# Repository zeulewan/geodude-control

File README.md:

# GEO-DUDe Control

Hardware photo:

GUI demo:

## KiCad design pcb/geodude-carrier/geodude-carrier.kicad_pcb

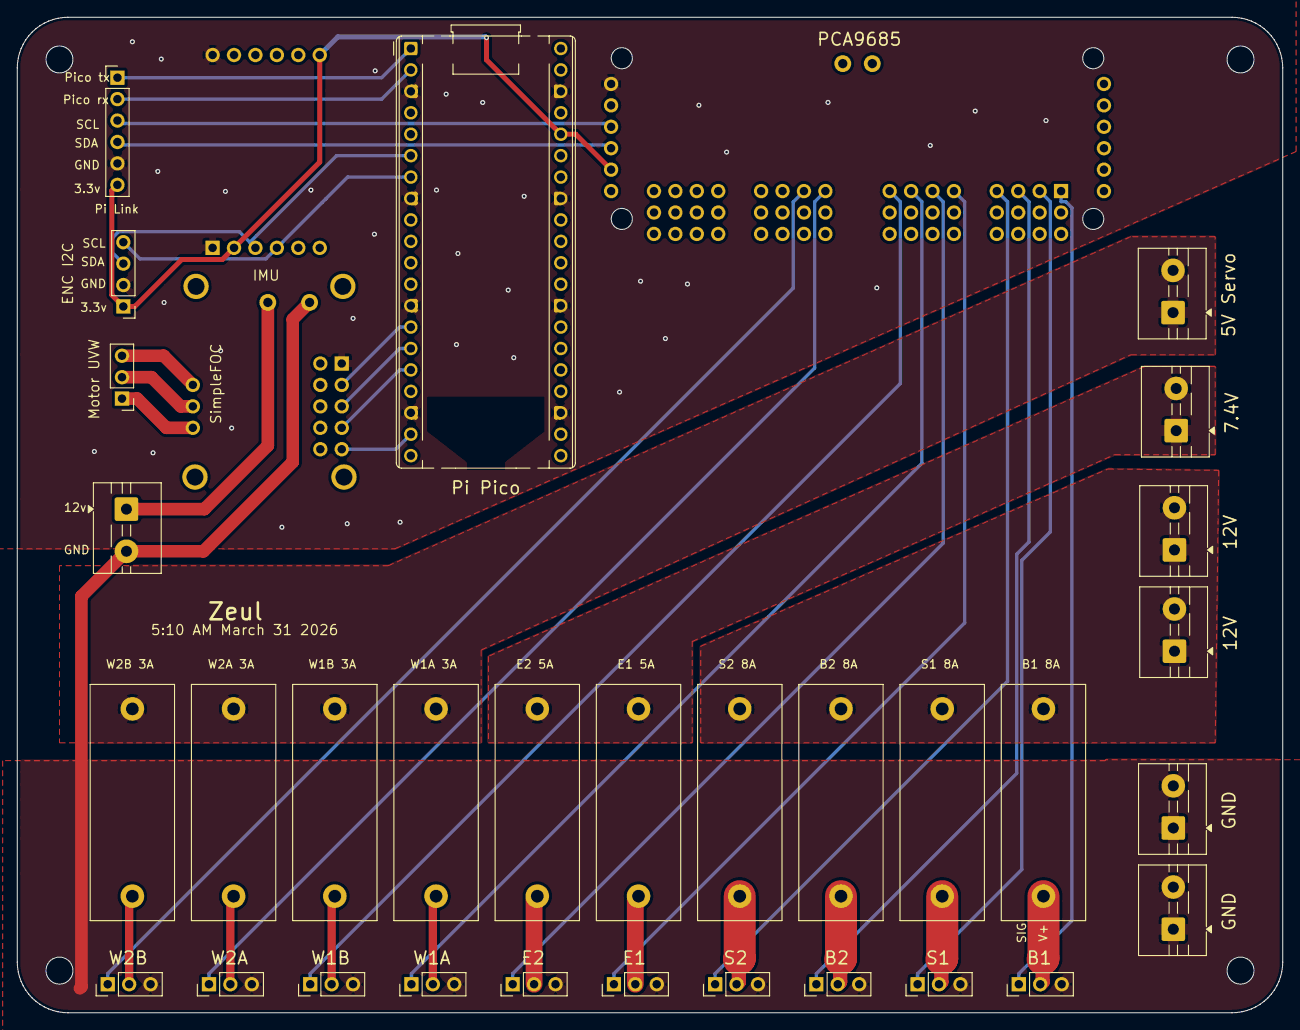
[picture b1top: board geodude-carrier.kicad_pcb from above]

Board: 2 copper layers, 150.0 x 118.0 mm, 38 parts (1 on the bottom side), 40 nets.

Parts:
F1: B1 8A; BLX-A_5x20mm
F2: S1 8A; BLX-A_5x20mm
F3: E1 5A; BLX-A_5x20mm
F4: W1A 3A; BLX-A_5x20mm
F5: W1B 3A; BLX-A_5x20mm
F6: B2 8A; BLX-A_5x20mm
F7: S2 8A; BLX-A_5x20mm
F8: E2 5A; BLX-A_5x20mm
F9: W2A 3A; BLX-A_5x20mm
F10: W2B 3A; BLX-A_5x20mm
J1, J2: 12V; TerminalBlock_MaiXu_MX126-5.0-02P_1x02_P5.00mm
J3, J4: GND; TerminalBlock_MaiXu_MX126-5.0-02P_1x02_P5.00mm
J5: 7.4V; TerminalBlock_MaiXu_MX126-5.0-02P_1x02_P5.00mm
J6: 5V Servo; TerminalBlock_MaiXu_MX126-5.0-02P_1x02_P5.00mm
J_ENC: ENC I2C; PinHeader_1x04_P2.54mm_Vertical
J_FOC: SimpleFOC; SimpleFOC_Mini
J_FOC_12V: 12V FOC; TerminalBlock_MaiXu_MX126-5.0-02P_1x02_P5.00mm
J_IMU: IMU; SparkFun_ICM20948
J_MOTOR: Motor UVW; PinHeader_1x03_P2.54mm_Vertical
J_PCA: PCA9685; PCA9685_Breakout
J_PICO: Pi Pico; RaspberryPi_Pico_Common_THT
J_SERIAL: Pi Link; PinHeader_1x06_P2.54mm_Vertical
MH1, MH2, MH3, MH4: M3; MountingHole_3.2mm_M3
SV1: B1; PinHeader_1x03_P2.54mm_Vertical
SV2: S1; PinHeader_1x03_P2.54mm_Vertical
SV3: E1; PinHeader_1x03_P2.54mm_Vertical
SV4: W1A; PinHeader_1x03_P2.54mm_Vertical
SV5: W1B; PinHeader_1x03_P2.54mm_Vertical
SV6: B2; PinHeader_1x03_P2.54mm_Vertical
SV7: S2; PinHeader_1x03_P2.54mm_Vertical
SV8: E2; PinHeader_1x03_P2.54mm_Vertical
SV9: W2A; PinHeader_1x03_P2.54mm_Vertical
SV10: W2B; PinHeader_1x03_P2.54mm_Vertical

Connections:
+3V3: J_ENC.1, J_IMU.2, J_IMU.12, J_PCA.56, J_PICO.36, J_SERIAL.6
+5V_SERVO: F4.1, F5.1, F9.1, F10.1, J6.1, J6.2
+7V4: F3.1, F8.1, J5.1, J5.2
+12V: F1.1, F2.1, F6.1, F7.1, J1.1, J1.2, J2.1, J2.2
+12V_FOC: J_FOC.15, J_FOC_12V.1
FOC_EN: J_FOC.3, J_PICO.14
FOC_IN1: J_FOC.9, J_PICO.19
FOC_IN2: J_FOC.7, J_PICO.16
FOC_IN3: J_FOC.5, J_PICO.15
GND: J3.1, J3.2, J4.1, J4.2, J_FOC.14, J_FOC_12V.2, SV1.3, SV2.3, SV3.3, SV4.3, SV5.3, SV6.3, SV7.3, SV8.3, SV9.3, SV10.3
GND_LOGIC: J_ENC.2, J_FOC.1, J_IMU.1, J_IMU.7, J_PCA.60, J_PICO.3, J_PICO.8, J_PICO.13, J_PICO.18, J_PICO.23, J_PICO.28, J_PICO.33, J_PICO.38, J_SERIAL.5
MOTOR_U: J_FOC.11, J_MOTOR.3
MOTOR_V: J_FOC.12, J_MOTOR.2
MOTOR_W: J_FOC.13, J_MOTOR.1
PICO_RX: J_PICO.2, J_SERIAL.2
PICO_SCL: J_ENC.4, J_IMU.4, J_PICO.7
PICO_SDA: J_ENC.3, J_IMU.3, J_PICO.6
PICO_TX: J_PICO.1, J_SERIAL.1
PWM_CH0: J_PCA.1, SV1.1
PWM_CH1: J_PCA.4, SV2.1
PWM_CH2: J_PCA.7, SV6.1
PWM_CH3: J_PCA.10, SV7.1
PWM_CH4: J_PCA.13, SV3.1
PWM_CH5: J_PCA.16, SV8.1
PWM_CH6: J_PCA.19, SV4.1
PWM_CH7: J_PCA.22, SV5.1
PWM_CH8: J_PCA.25, SV9.1
PWM_CH9: J_PCA.28, SV10.1
SCL: J_PCA.58, J_SERIAL.3
SDA: J_PCA.57, J_SERIAL.4
SV1_PWR: F1.2, SV1.2
SV2_PWR: F2.2, SV2.2
SV3_PWR: F3.2, SV3.2
SV4_PWR: F4.2, SV4.2
SV5_PWR: F5.2, SV5.2
SV6_PWR: F6.2, SV6.2
SV7_PWR: F7.2, SV7.2
SV8_PWR: F8.2, SV8.2
SV9_PWR: F9.2, SV9.2
SV10_PWR: F10.2, SV10.2

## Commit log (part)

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2026-03-24 cd /home/mizi/geodude-dev/groundstationAdd camera stream toggle to dashboard fuser -k 8081/tcp || true (env WHEEL_CONTROL_PORT=8081 WHEEL_CONTROL_DRY_RUN=1 WHEEL_CONTROL_RESTORE_ON_START=0 nohup pyth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
2026-03-24 Bias dev IK toward stiffer wrist-assisted poses
2026-03-24 Update dev mission simulation flow
2026-03-24 Compact dev mission simulation layout
2026-03-24 Add EN active LOW and MS1/MS2 address table to TMC2209 driver label
2026-03-24 Fix screw terminal count: 2x 7.4V and 2x 5V inputs
2026-03-24 Add dev mission substep completion states
2026-03-25 Add dev approach arm positioning substeps
2026-03-25 Add dev AOCS attach mission substeps
2026-03-25 Enable mission arm view mouse controls
2026-03-25 Reorder dev identified-check substeps
2026-03-25 Checkpoint MACE control updates before branch merge
2026-03-25 MACE: RPM input, enable/disable/stop/calibrate buttons, voltage limit
2026-03-27 Fix All Neutral button: send PWM command to hardware
    chGoNeutral() was only updating the slider UI without calling
    chSendPwm(), so the button had no effect on actual servo positions.
2026-03-27 Gimbal firmware: OTA resilience, POST /reboot, driverFound cache, UART race guards
    Firmware (firmware/esp32/gimbal_controller.ino):
    - Cache per-driver found state (driverFound[4]); handleStatus returns the cached
    value during stepping so the dashboard stops flashing NOT FOUND while a motor
    is actually moving.
    - handleMotorIhold now applies the change to the driver immediately when the
    motor is idle-but-enabled. Previously the value was only stored in RAM and
2026-03-27 Servo safety v4: second audit findings (C-A, C-B, H-A..E, L-B, L-D, L-E, M-C..F)
    Second paranoid audit found that v3 still left a few holes. These fixes
    close them all.
    CRITICAL fixes:
    - C-A: Groundstation no longer blindly trusts accepted_pw returned from
    GEO-DUDe. Clamp to [0..2500] and to the per-channel envelope before
    assigning it to _servo_actual_pw. If the remote somehow returns a value
2026-03-27 Add pwm_seed to prevent 50us staircase on unpowered channels
    GEO-DUDe:
    - New POST /pwm_seed writes a requested pw directly to the PCA and sets
    _servo_last_pw in one step. Only accepted when the channel is currently
    unseeded (last_pw is None or 0); rejected with 409 if a live signal is
    present. Cannot be used to bypass the 50us delta clamp on a moving servo.
    Groundstation:
2026-03-30 Camera: 1280x960 4:3 uncropped
2026-03-30 Add brake button and RPM display
    Brake: sends 1000us (idle) but stays armed - ESC applies brake if enabled
    RPM: calculated from encoder angle deltas, 15-sample rolling average
2026-03-30 Fix arm button flicker: skip DOM updates when state unchanged
2026-03-30 Revert sensor loop to 30Hz — 100Hz caused I2C lock contention with motor writes
2026-03-30 Update gimbal ESP32 docs: pin assignments, UART wiring, network config
    - Corrected STEP/DIR pin assignments to match firmware (GPIO 32/33, 25/26, 23/22, 19/18)
    - Added UART pin assignment: GPIO 16 (RX) / GPIO 17 (TX) with 1K resistor
    - Documented BTT TMC2209 V1.3 single-wire UART wiring (factory default RX pin only)
    - Added ESP32 firmware details: web UI, OTA, WiFi, driver scanning, motor control
    - Added note that 24V on VM is required for UART communication
    - Updated base station with hostname, WiFi hotspot config, network architecture
2026-03-30 Fix carrier PCB schematic: 5 power rails, PCA9685 on 3.3V
    - +12V (servo power, ESC, fan)
    - +7V4 (elbow servo power)
    - +5V_SERVO (wrist servo power, from buck 3)
    - +5V_LOGIC (from Pi 5V, general purpose)
    - +3V3 (from Pi 3.3V, PCA9685 VCC, I2C bus)
2026-03-30 Generated netlist from SKiDL - all components and nets verified
2026-03-30 Custom BLX-A fuse footprint, updated PCB layout with paralleled 12V/GND
2026-03-30 Disable manual routing (traces cross), prepare for Freerouting
2026-03-30 Remove broken net class API call, widths via DSN patching only
2026-03-30 Replace single pin headers with 1x4 headers for bus section
2026-03-30 All power screw terminals in one line at top edge
2026-03-30 Layout: logic bus left edge, servo headers right edge, PCA top edge
2026-03-30 Logic bus: screw terminals in column left, headers column right
2026-03-30 Centre PCA socket properly (account for pin 1 origin offset)
2026-03-30 Centre servo row, centre ESC/Fan, bring fuses closer
2026-03-30 Sync generate_pcb.py: remove GND terminals
2026-03-30 Fix SV10 position, snap all components to grid
2026-03-30 Clean re-route: 254 tracks, no shorts, J1/J2 all +12V, silkscreen preserved
2026-03-30 Re-routed with default clearance, 2 unconnected remaining, via sizing needs work
2026-03-30 Add agent onboarding doc for new developers
2026-03-30 230 tracks, 1 unconnected (fan PWM - manual route needed), Gerbers updated
2026-03-30 Snap screw terminals in columns on each side
2026-03-30 Left bus: screw+header pairs aligned, 12mm spacing
2026-03-30 Routed, bigger silk, ESC/Fan fixed, Gerbers - 5 unconnected need manual route
2026-03-30 Wider board 128x149mm, 6mm rounded corners, fuses spread, 273 tracks, 0 unconnected
2026-03-30 Re-routed with adjusted edges, 253 tracks, 1 unconnected
2026-03-31 Board 140x134mm, fan +12V thin trace, render, 1 unconnected PWM, Gerbers ready
2026-03-31 Carrier PCB docs: SimpleFOC system, Pi Pico, IMU breakout, remove ESC
2026-03-31 Stripped for placement work
2026-03-31 Add deceleration ramp for smooth motor stopping
    Trapezoidal velocity profile: accelerate from 8000us to target
    step delay, cruise, then decelerate symmetrically. Prevents
    abrupt stops that caused motor oscillation on longer moves.
2026-03-31 Fix IHOLD=0: move begin() out of doScan() to prevent reset
    doScan() was calling begin() on all drivers, which reinitialized
    them and overwrote the IHOLD=0 register write. Split into
    initDrivers() (called once at boot) and doScan() (read-only).
2026-03-31 Revamp UI: tabbed layout, compact header, full gimbal parity
    - Tabbed navigation: GEO-DUDe / Gimbal / Servos
    - Always-visible header: camera (400px), system stats, sensor strip
    - Dual connection status dots (GEO-DUDe + Gimbal)
    - Wider layout (1200px max)
    - Gimbal tab: speed presets, current input, per-driver detail
    cards with OT/OTPW warnings, collapsible driver info,
2026-03-31 More compact: tighter padding, margins, gaps, font sizes
2026-03-31 Fix idle heating: force SpreadCycle + toff(0) at boot before any autoscale
2026-03-31 Smoother ramp: 4000us start (was 8000), 15% accel phase (was 25%)
2026-03-31 Add PCB agent onboarding docs (pcb/CLAUDE.md)
2026-04-01 Rate-limit servo slider movements with max velocity
    Slider drags no longer send PWM directly. A continuous ramp
    loop (30Hz) moves actual PWM toward the slider target at the
    configured max speed. Prevents jerky servo movements when
    dragging sliders quickly. Center and Neutral buttons also go
    through the same rate-limited path.
2026-04-01 Add ramp rate slider, persist speed settings, fix camera multi-client
    - Ramp rate slider back (controls center/neutral button speed)
    - Servo speed + ramp rate persist in localStorage across reloads
    - Camera: single reader thread fans out frames to all clients,
    fixes stream corruption when multiple browsers connect
2026-04-01 Store servo neutral positions server-side on disk
    Neutral positions saved to servo_neutral.json on the groundstation
    Pi. Survives page reloads, browser changes, and reboots.
2026-04-01 Order servos as Arm 1 (left) and Arm 2 (right) columns
2026-04-01 Safe servo startup: neutral on boot, remove dangerous center
    - sensor_server: remove pca_all_off() on boot, let groundstation
    send neutral positions instead of leaving servos limp
    - Restore loop sends neutral positions, not last-known
    - chActual defaults to neutral, not 1500
    - Remove ALL CENTER button and per-servo Center button (1500us
    fully extends arms, dangerous)
2026-04-01 Document network architecture, git workflow, multi-developer setup
2026-04-02 Refactor MACE reaction wheel control from ESC/PCA9685 to SimpleFOC/Pico USB serial
    - geodude/sensor_server.py: add /simplefoc endpoint that sends velocity commands
    to Pi Pico over USB serial (/dev/ttyACM0, 115200 baud) using SimpleFOC Commander
    protocol (T<value>\n). Legacy /motor endpoint kept, translates ESC PWM to velocity.
    - groundstation/wheel_control.py: replace ESC PWM logic with velocity (rad/s) control.
    send_motor() -> send_velocity(), /api/throttle -> /api/velocity, /api/arm now
    instantly enables/disables (no 3s ESC arm sequence), /api/calibrate removed,
2026-04-03 Pico SimpleFOC firmware: streaming telemetry, I2C1 sensors, loopFOC fix
2026-04-04 Update CLAUDE.md: full MACE SimpleFOC docs, analog encoder, hardware notes, telemetry format
2026-04-07 Run competition vision inference on laptop dev server
2026-04-07 Add Nucleo F446RE firmware, attitude controller, and development log
    - nucleo/nucleo-simplefoc.ino: SimpleFOC for STM32F446RE + Shield V2.0.4
    - MT6701 encoder (ABZ, 1024 PPR), ICM20948 IMU (I2C)
    - Velocity and torque modes, motor disabled on boot
    - 50Hz JSON telemetry, full serial command set
    - geodude/attitude_controller.py: single PID (angle -> voltage)
    - Auto gyro calibration, torque mode switching, motor safety
2026-04-08 Reconcile Mizi competition centering UI
2026-04-08 Keep sensor server alive if PCA init fails
2026-04-21 Add minimal momentary MACE jog controls
2026-04-21 Fix reaction wheel hold button races
2026-04-21 Reaction wheel: fire-and-forget on jog hot path
    Press/release latency was dominated by serial read_for waits for replies
    the firmware never sends while armed. Switch T/E on start, D on release,
    and the MR/V/R config push to fire-and-forget writes (write+flush, no
    read loop). Caller still holds pico_lock during the write, so no serial
    races; any status lines the firmware does emit get picked up by the next
    actual read (status poll, calibrate).
2026-04-21 Fix gimbal idle current handling
2026-04-21 Add gimbal StealthChop and interpolation toggles
2026-04-21 Add gimbal step timing debug readout
2026-04-22 Wrap gimbal angle display and refresh faster
2026-04-22 Make gimbal zero semantics axis-specific
2026-04-22 Broaden gimbal limit defaults for GUI setup
2026-04-22 Shift control palette to warm graphite
2026-04-22 Add Alloy gimbal handoff doc
2026-04-22 Update Alloy handoff for tumble mode
2026-04-22 gitignore: exclude all runtime servo state files
    servo_setpoints.json, servo_limits.json, and joint_calibration.json
    are per-deployment runtime data, same concern as the already-ignored
    servo_neutral.json and servo_positions.json.
2026-04-22 docs: update ADAM_HANDOFF for setpoints, actions, heartbeat, safety
    Covers everything shipped since the first handoff was written:
    - Setpoints: capture/rename/delete/go, pw>=500 gates, bootstrap
    complete gate, file persistence, backend+frontend symbols.
    - Actions: ordered setpoint sequences, breakpoints, ALL NEUTRAL
    pseudo-setpoint, play/stop/continue lifecycle, playback worker
    deep-copy, pw<500 defensive check in apply, freeze-on-stop,
2026-04-23 Reaction wheel: default jog controls to max
    Make the MACE jog path default to 24V and 2000 rad/s^2 across the UI, groundstation proxy, GEO-DUDe backend, and Nucleo firmware.
    Also keep the narrowed MACE hold-button safety fixes in the same app.js slice so false releases do not regress while the new defaults ship.
2026-04-23 Use live gimbal tumble config for procedures
2026-04-23 Accept wrapped zero on procedure return
2026-04-23 Remove servo calibration UI and bulk-zero procedures
